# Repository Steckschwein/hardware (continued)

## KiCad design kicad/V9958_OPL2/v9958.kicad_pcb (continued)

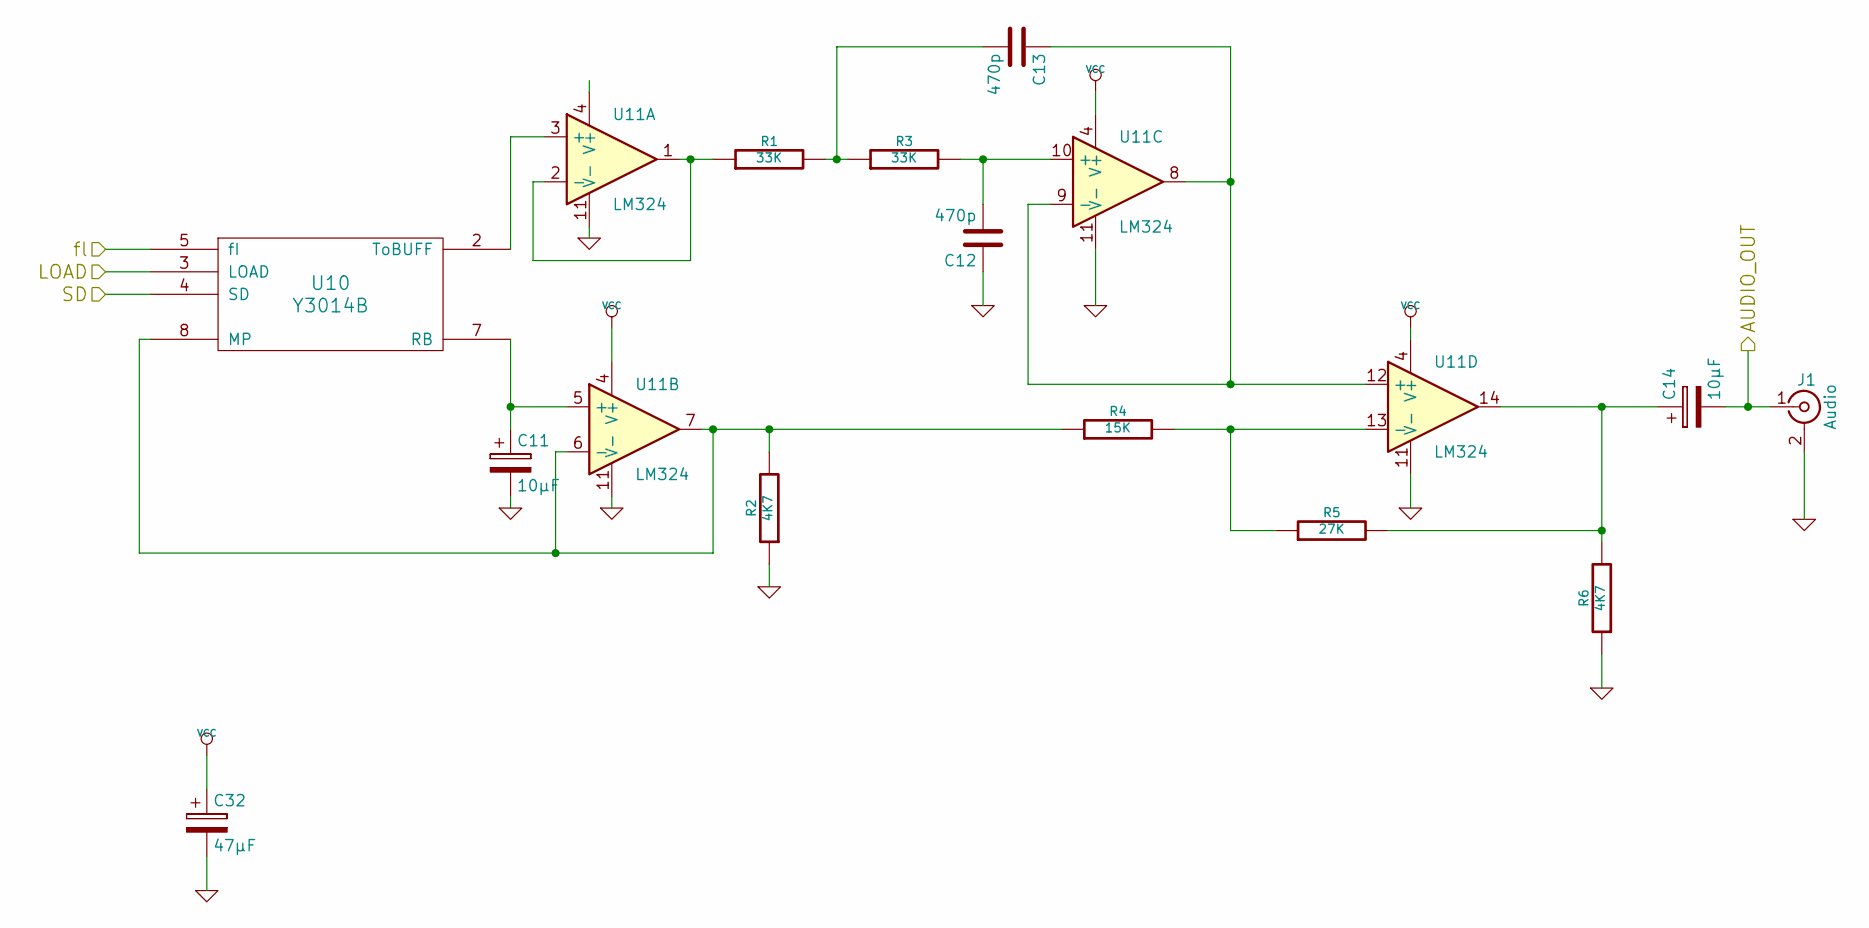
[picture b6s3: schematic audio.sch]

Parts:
C11, C14: 10µF; CP_Radial_D6.3mm_P2.50mm
C12, C13: 470p; C_Disc_D3.0mm_W1.6mm_P2.50mm
C32: 47µF; CP_Radial_D6.3mm_P2.50mm
J1: Audio; rca
R1, R3: 33K; R3
R2, R6: 4K7; R3
R4: 15K; R3
R5: 27K; R3
U10: Y3014B; DIP-8_W7.62mm_LongPads
U11: LM324; DIP-14_W7.62mm_LongPads

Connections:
/Audio/AUDIO_OUT: C14.2, J1.1 (In); also elsewhere on the board
/Audio/LOAD: U10.3 (LOAD); also elsewhere on the board
/Audio/SD: U10.4 (SD); also elsewhere on the board
/Audio/fl: U10.5 (fI); also elsewhere on the board
GND: C11.2, C12.1, C32.2, J1.2 (Ext), R2.1, R6.1, U10.6 (GND), U11.11 (V-); also elsewhere on the board
unnamed: C11.1, U10.7 (RB), U11.5 (+)
unnamed: C12.2, R3.2, U11.10 (+)
unnamed: C13.1, U11.8, U11.9 (-), U11.12 (+)
unnamed: C13.2, R1.2, R3.1
unnamed: C14.1, R5.2, R6.2, U11.14
unnamed: R1.1, U11.1, U11.2 (-)
unnamed: R2.2, R4.1, U10.8 (MP), U11.6 (-), U11.7
unnamed: R4.2, R5.1, U11.13 (-)
unnamed: U10.2 (ToBUFF), U11.3 (+)
VCC: C32.1, U10.1 (VCC), U11.4 (V+); also elsewhere on the board

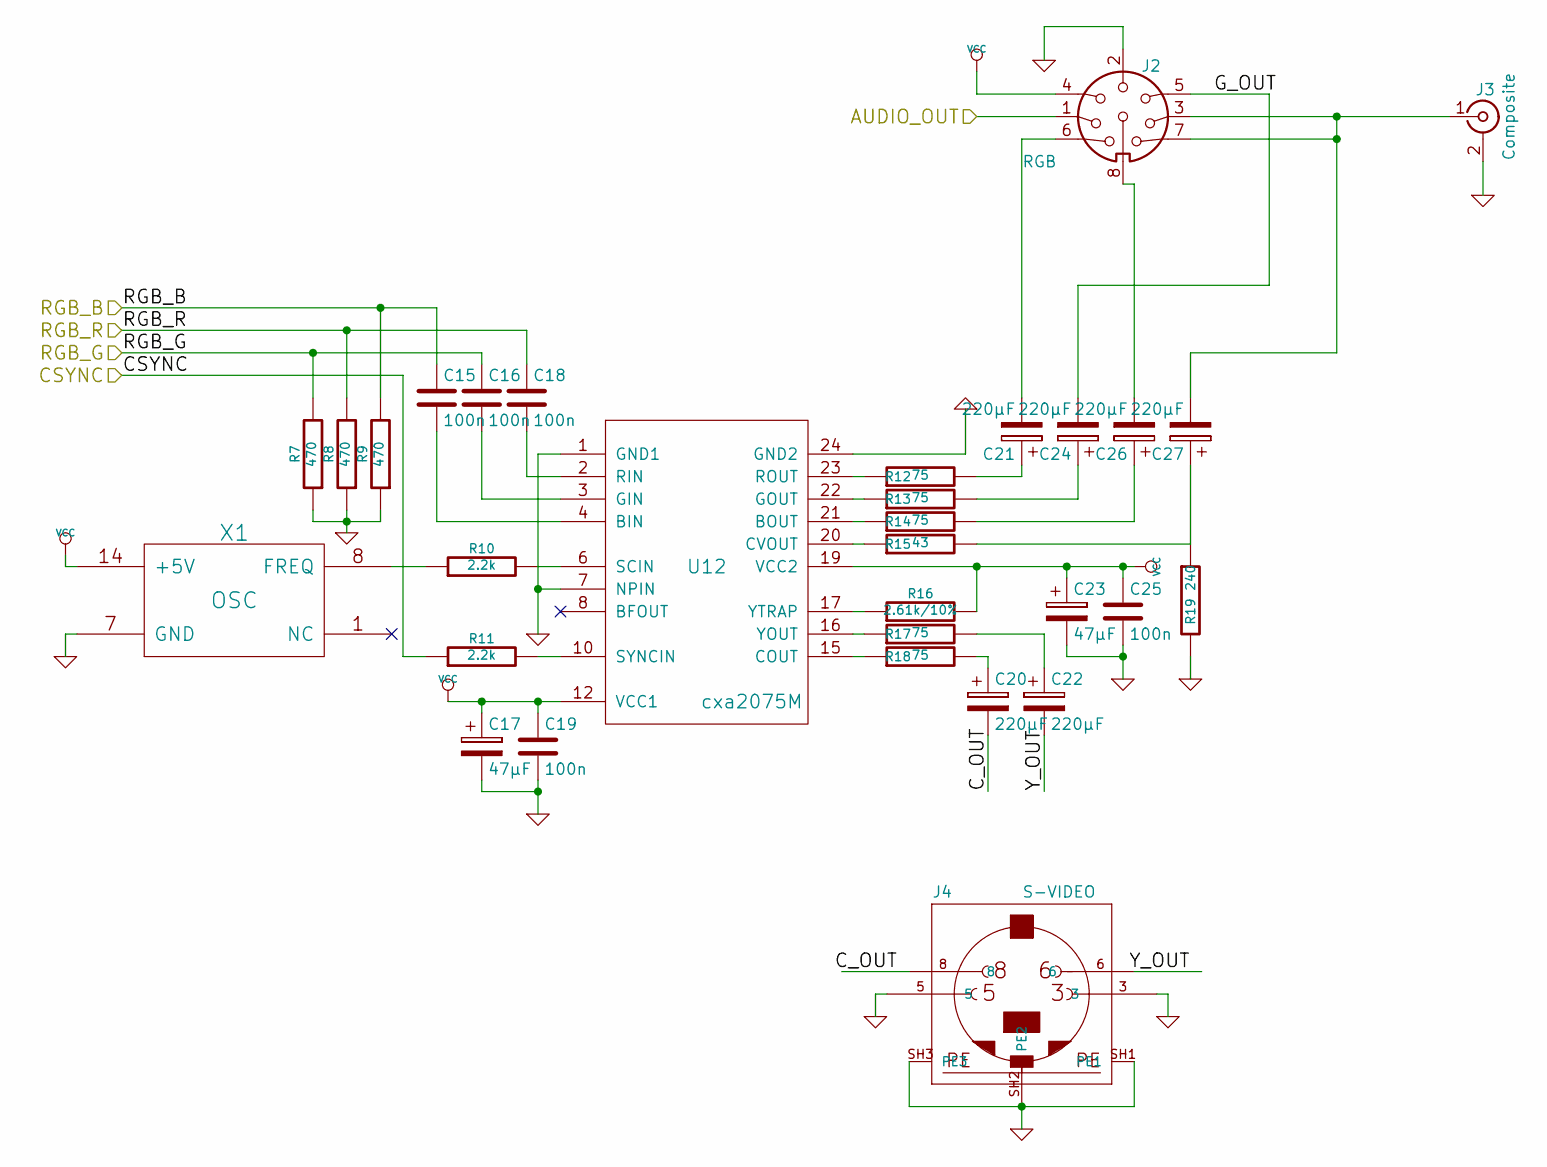
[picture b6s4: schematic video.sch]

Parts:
C15, C16, C18, C19: 100n; C_Disc_D3.0mm_W1.6mm_P2.50mm
C17, C23: 47µF; CP_Radial_D6.3mm_P2.50mm
C20, C21, C22, C24, C26, C27: 220µF; CP_Radial_D6.3mm_P2.50mm
C25: 100n; C_Disc_D3.0mm_W2.0mm_P2.50mm
J2: RGB; DIN-8
J3: Composite; rca
J4: S-VIDEO; mini_din-M_DIN4
R7, R8, R9: 470; R3
R10, R11: 2.2k; R3
R12, R13, R14, R17, R18: 75; R3
R15: 43; R3
R16: 2.61k/10%; R3
R19: 240; R3
U12: cxa2075M; SOIC-24W_7.5x15.4mm_Pitch1.27mm
X1: OSC; Oscillator_DIP-14_LargePads

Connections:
/Audio/AUDIO_OUT: J2.1; also elsewhere on the board
/CSYNC: R11.1; also elsewhere on the board
/RGB_B: C15.1, R9.2; also elsewhere on the board
/RGB_G: C16.1, R7.2; also elsewhere on the board
/RGB_R: C18.1, R8.2; also elsewhere on the board
/Video/C_OUT: C20.2, J4.8
/Video/G_OUT: C24.2, J2.5
/Video/Y_OUT: C22.2, J4.6
GND: C17.2, C19.2, C23.2, C25.2, J2.2, J3.2 (Ext), J4.3, J4.5, J4.SH1 (PE1), J4.SH2 (PE2), J4.SH3 (PE3), R7.1, R8.1, R9.1, R19.2, U12.1 (GND1), U12.7 (NPIN), U12.24 (GND2), X1.7 (GND); also elsewhere on the board
unnamed: C15.2, U12.4 (BIN)
unnamed: C16.2, U12.3 (GIN)
unnamed: C18.2, U12.2 (RIN)
unnamed: C20.1, R18.2
unnamed: C21.1, R12.2
unnamed: C21.2, J2.6
unnamed: C22.1, R17.2
unnamed: C24.1, R13.2
unnamed: C26.1, R14.2
unnamed: C26.2, J2.8
unnamed: C27.1, R15.2, R19.1
unnamed: C27.2, J2.3, J2.7, J3.1 (In)
unnamed: R10.1, X1.8 (FREQ)
unnamed: R10.2, U12.6 (SCIN)
unnamed: R11.2, U12.10 (SYNCIN)
unnamed: R12.1, U12.23 (ROUT)
unnamed: R13.1, U12.22 (GOUT)
unnamed: R14.1, U12.21 (BOUT)
unnamed: R15.1, U12.20 (CVOUT)
unnamed: R16.1, U12.17 (YTRAP)
unnamed: R17.1, U12.16 (YOUT)
unnamed: R18.1, U12.15 (COUT)
VCC: C17.1, C19.1, C23.1, C25.1, J2.4, R16.2, U12.12 (VCC1), U12.19 (VCC2), X1.14 (+5V); also elsewhere on the board

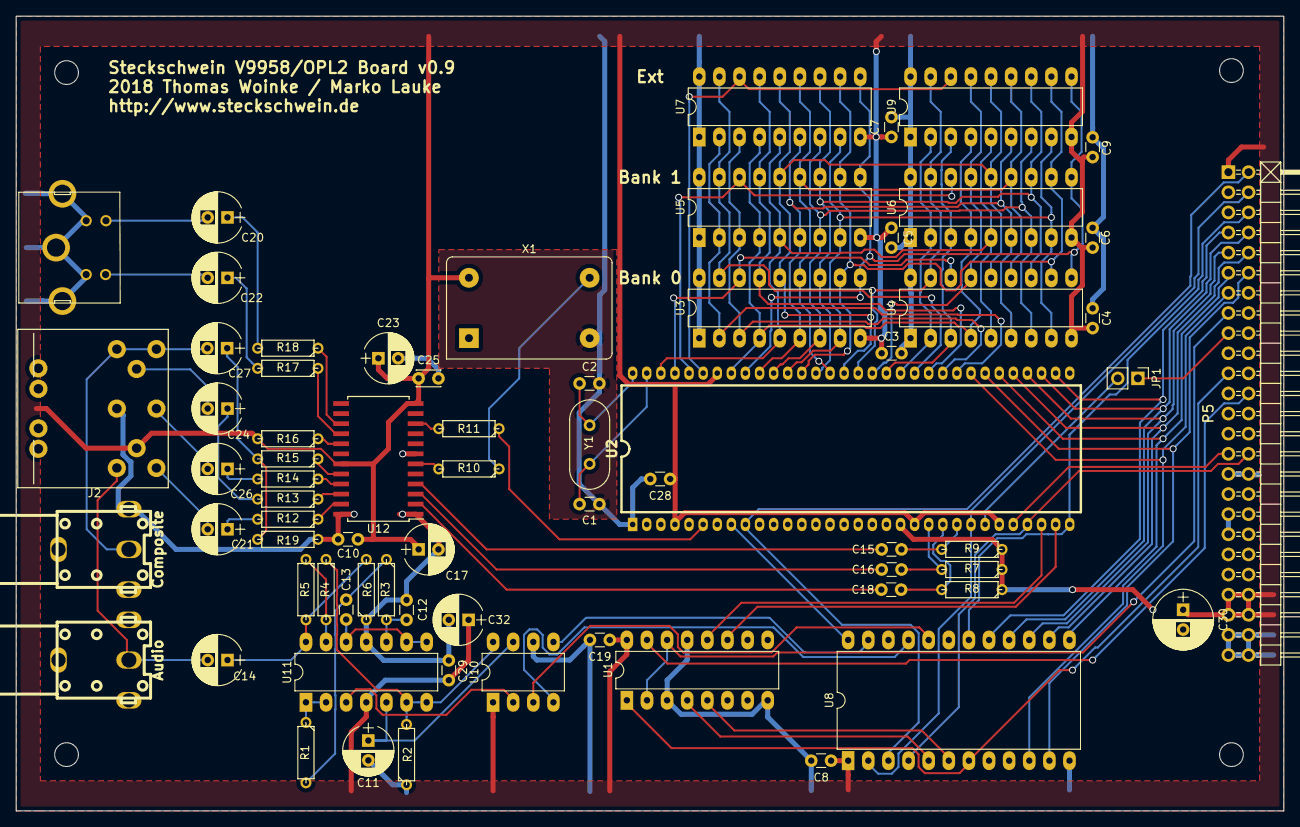
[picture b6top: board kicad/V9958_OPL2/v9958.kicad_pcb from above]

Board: 2 copper layers, 160.0 x 100.3 mm, 74 parts (0 on the bottom side), 89 nets.

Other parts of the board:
MH1, MH2, MH3, MH4: MountingHole_3mm_RevA_Date21Jun2010; MountingHole_3mm

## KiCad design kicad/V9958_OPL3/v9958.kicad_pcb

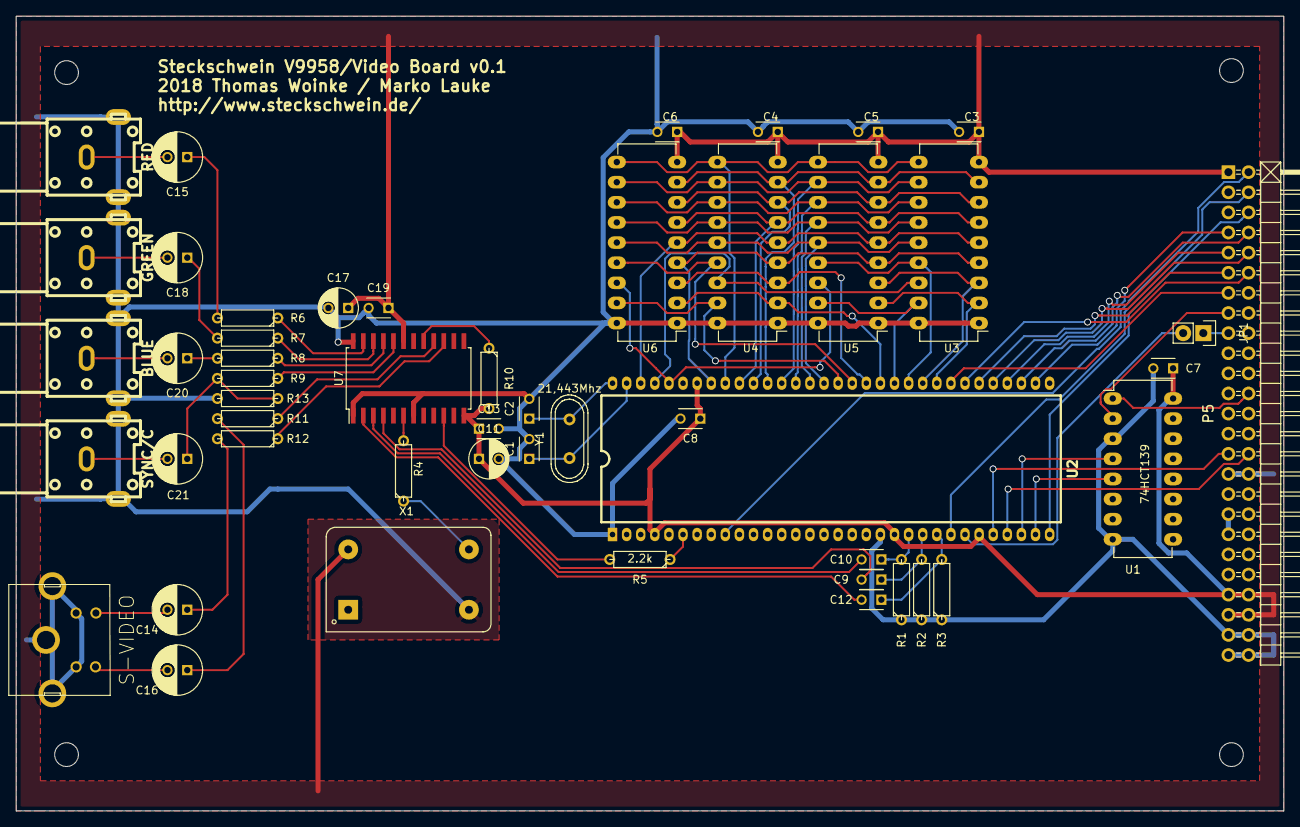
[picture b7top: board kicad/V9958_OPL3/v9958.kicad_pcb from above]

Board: 2 copper layers, 160.0 x 100.3 mm, 54 parts (0 on the bottom side), 71 nets.

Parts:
C1, C2: 22p; C_Disc_D3_P2.5
C3, C4, C5, C6, C7, C8, C9, C10, C12, C13, C19: 100n; C_Disc_D3_P2.5
C11, C17: 47µF; C_Radial_D5_L11_P2.5
C14, C15, C16, C18, C20, C21: 220µF; C_Radial_D6.3_L11.2_P2.5
JP1: JUMPER; Pin_Header_Straight_1x02
MH1, MH2, MH3, MH4: MountingHole_3mm_RevA_Date21Jun2010; MountingHole_3mm
P1: RED; rca_black
P2: GREEN; rca_black
P3: BLUE; rca_black
P4: SYNC/C; rca_black
P5: CONN_02X25; Pin_Header_Angled_2x25
R1, R2, R3: 470; R3
R4, R5: 2.2k; R3
R6, R7, R8, R11, R12: 75; R3
R9: 43; R3
R10: 2.61k/10%; R3
R13: 240; R3
U1: 74HCT139; DIP-16_W7.62mm_LongPads
U2: V9958; SDIP64
U3, U4, U5, U6: DRAM_64KX4; DIP-18_W7.62mm_LongPads
U7: cxa2075M; SOIC-24_7.5x15.4mm_Pitch1.27mm
X1: OSC; KXO-200_LargePads
X2: S-VIDEO; mini_din-M_DIN4
Y1: 21,443Mhz; Crystal_HC49-U_Vertical

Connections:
/50pin connector/A0: P5.30, U2.29
/50pin connector/A1: P5.29, U2.28
/50pin connector/D0: P5.13, U2.40
/50pin connector/D1: P5.12, U2.39
/50pin connector/D2: P5.11, U2.38
/50pin connector/D3: P5.10, U2.37
/50pin connector/D4: P5.9, U2.36
/50pin connector/D5: P5.8, U2.35
/50pin connector/D6: P5.7, U2.34
/50pin connector/D7: P5.6, U2.32
//CAS0: U2.61, U3.16, U4.16
//CAS1: U2.60, U5.16, U6.16
//RAS: U2.62, U3.5, U4.5, U5.5, U6.5
/AD0: U2.49, U3.14, U4.14, U5.14, U6.14
/AD1: U2.50, U3.13, U4.13, U5.13, U6.13
/AD2: U2.51, U3.12, U4.12, U5.12, U6.12
/AD3: U2.52, U3.11, U4.11, U5.11, U6.11
/AD4: U2.53, U3.8, U4.8, U5.8, U6.8
/AD5: U2.54, U3.7, U4.7, U5.7, U6.7
/AD6: U2.55, U3.6, U4.6, U5.6, U6.6
/AD7: U2.56, U3.10, U4.10, U5.10, U6.10
/CSYNC: R5.1, U2.6
/CS_VDP: P5.24, U1.1
/C_OUT: C14.2, X2.8
/IRQ: P5.4, U2.25
/R/W: U2.57, U3.4, U4.4, U5.4, U6.4
/RD0: U2.41, U3.2, U5.2
/RD1: U2.42, U3.3, U5.3
/RD2: U2.43, U3.15, U5.15
/RD3: U2.44, U3.17, U5.17
/RD4: U2.45, U4.2, U6.2
/RD5: U2.46, U4.3, U6.3
/RD6: U2.47, U4.15, U6.15
/RD7: U2.48, U4.17, U6.17
/RESET: P5.2, U2.9
/RGB_B: C12.1, R3.2, U2.24
/RGB_G: C10.1, R1.2, U2.22
/RGB_R: C9.1, R2.2, U2.23
/RW: P5.15, U1.2
/Y_OUT: C16.2, X2.6
GND: C1.2, C2.2, C3.2, C4.2, C5.2, C6.2, C7.2, C8.2, C11.2, C13.2, C17.2, C19.2, P1.2, P2.2, P3.2, P4.2, P5.31, P5.32, P5.35, P5.37, P5.47, P5.48, P5.49, P5.50, R1.1, R2.1, R3.1, R13.2, U1.3, U1.8, U2.1, U2.20, U3.1, U3.18, U4.1, U4.18, U5.1, U5.18, U6.1, U6.18, U7.1, U7.7, U7.24, X1.7, X2.3, X2.5, X2.SH1, X2.SH2, X2.SH3
unnamed: C1.1, U2.63, Y1.1
unnamed: C2.1, U2.64, Y1.2
unnamed: C9.2, U7.4
unnamed: C10.2, U7.3
unnamed: C12.2, U7.2
unnamed: C14.1, R12.2
unnamed: C15.1, R6.2
unnamed: C15.2, P1.1
unnamed: C16.1, R11.2
unnamed: C18.1, R7.2
unnamed: C18.2, P2.1
unnamed: C20.1, R8.2
unnamed: C20.2, P3.1
unnamed: C21.1, R9.2, R13.1
unnamed: C21.2, P4.1
unnamed: JP1.2, U2.26
unnamed: R4.1, X1.8
unnamed: R4.2, U7.6
unnamed: R5.2, U7.10
unnamed: R6.1, U7.23
unnamed: R7.1, U7.22
unnamed: R8.1, U7.21
unnamed: R9.1, U7.20
unnamed: R10.1, U7.17
unnamed: R11.1, U7.16
unnamed: R12.1, U7.15
unnamed: U1.4, U2.30
unnamed: U1.5, U2.31
RDY: JP1.1, P5.17
VCC: C3.1, C4.1, C5.1, C6.1, C7.1, C8.1, C11.1, C13.1, C17.1, C19.1, P5.1, P5.43, P5.44, P5.45, P5.46, R10.2, U1.16, U2.4, U2.21, U2.27, U2.58, U3.9, U4.9, U5.9, U6.9, U7.12, U7.19, X1.14

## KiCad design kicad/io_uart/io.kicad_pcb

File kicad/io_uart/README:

This is the IO-board with integrated UART.
This is the currently used board.

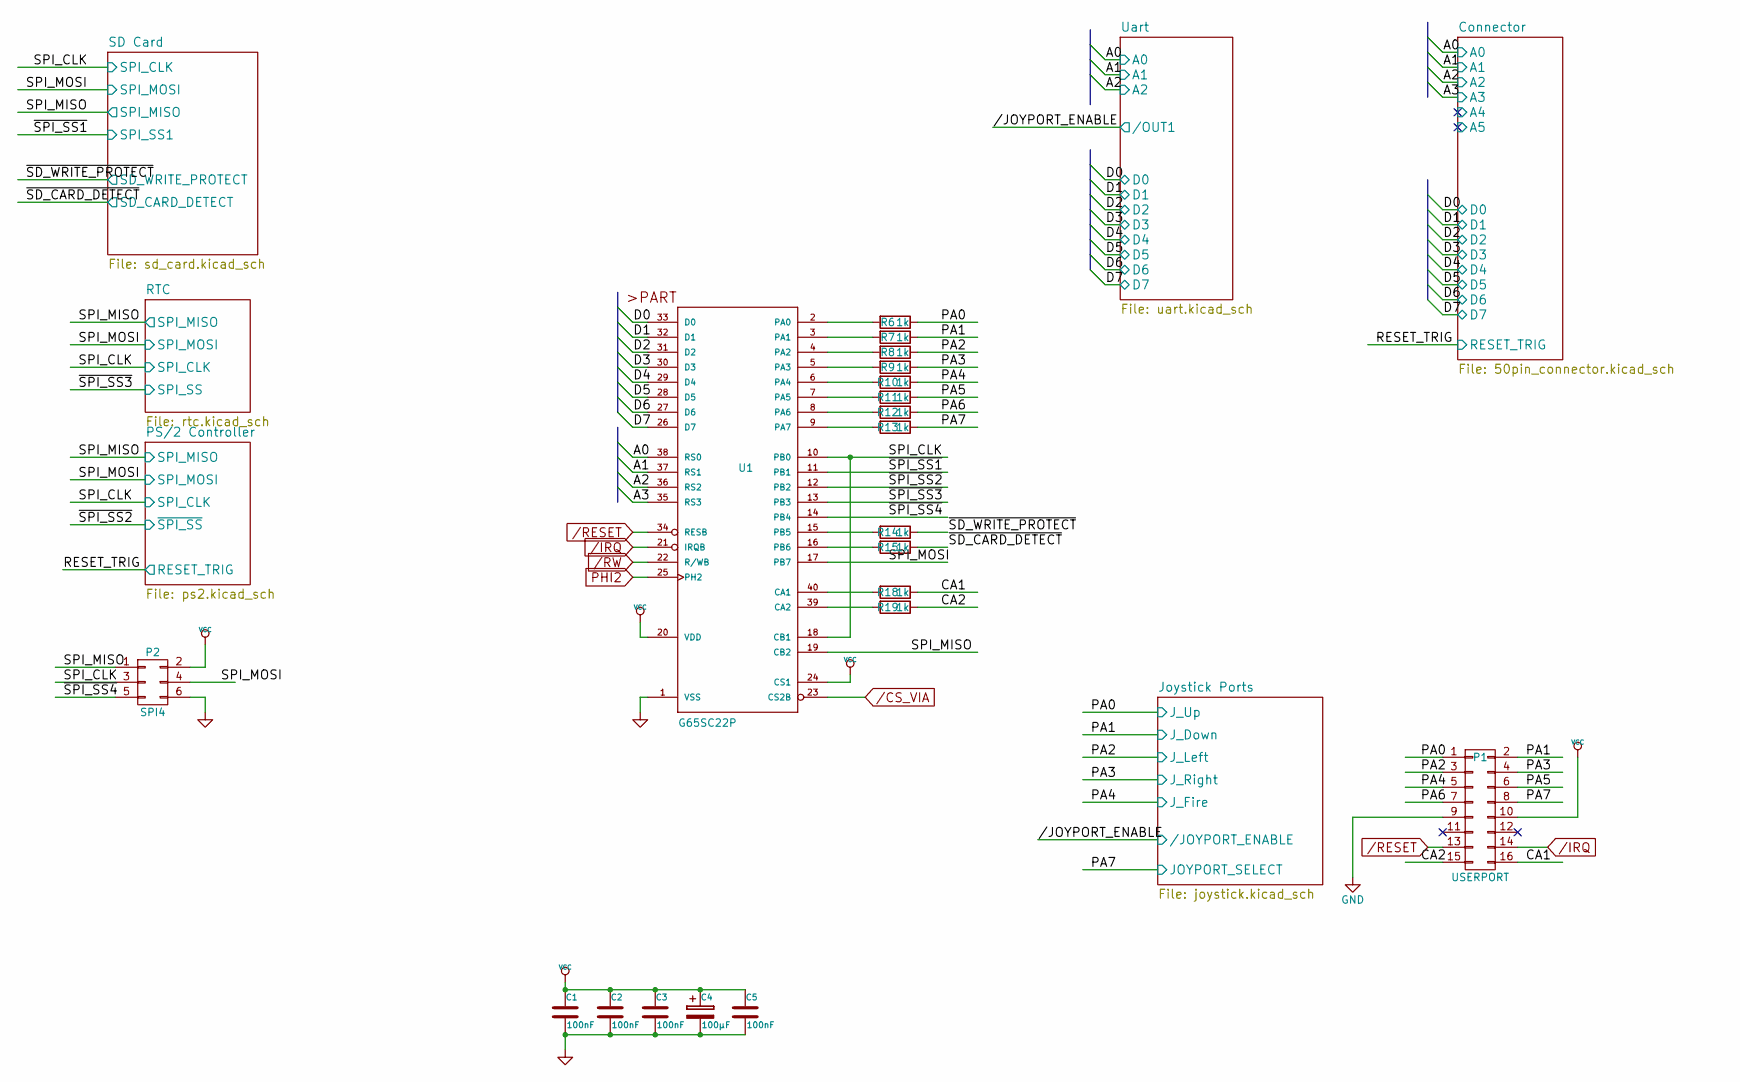
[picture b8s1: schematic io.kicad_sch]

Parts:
C1, C2, C3, C5: 100nF; C_Disc_D3_P2.5
C4: 100µF; C_Disc_D3_P2.5
P1: USERPORT; Pin_Header_Angled_2x08
P2: SPI4; Pin_Header_Angled_2x03
R6, R7, R8, R9, R10, R11, R12, R13, R14, R15, R18, R19: 1k; Resistor_Horizontal_RM7mm
U1: G65SC22P; DIP-40_W15.24mm_LongPads

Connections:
/CA1: P1.16, R18.1
/CA2: P1.15, R19.1
/CS_VIA: U1.23 (CS2B); also elsewhere on the board
/Connector/A0: U1.38 (RS0); also elsewhere on the board
/Connector/A1: U1.37 (RS1); also elsewhere on the board
/Connector/A2: U1.36 (RS2); also elsewhere on the board
/Connector/A3: U1.35 (RS3); also elsewhere on the board
/Connector/D0: U1.33 (D0); also elsewhere on the board
/Connector/D1: U1.32 (D1); also elsewhere on the board
/Connector/D2: U1.31 (D2); also elsewhere on the board
/Connector/D3: U1.30 (D3); also elsewhere on the board
/Connector/D4: U1.29 (D4); also elsewhere on the board
/Connector/D5: U1.28 (D5); also elsewhere on the board
/Connector/D6: U1.27 (D6); also elsewhere on the board
/Connector/D7: U1.26 (D7); also elsewhere on the board
/IRQ: P1.14, U1.21 (IRQB); also elsewhere on the board
/Joystick Ports/JOYPORT_SELECT: P1.8, R13.1; also elsewhere on the board
/Joystick Ports/J_Down: P1.2, R7.1; also elsewhere on the board
/Joystick Ports/J_Fire: P1.5, R10.1; also elsewhere on the board
/Joystick Ports/J_Left: P1.3, R8.1; also elsewhere on the board
/Joystick Ports/J_Right: P1.4, R9.1; also elsewhere on the board
/Joystick Ports/J_Up: P1.1, R6.1; also elsewhere on the board
/PA5: P1.6, R11.1
/PA6: P1.7, R12.1
/PS/2 Controller/SPI_CLK: P2.3, U1.10 (PB0), U1.18 (CB1); also elsewhere on the board
/PS/2 Controller/SPI_MISO: P2.1, U1.19 (CB2); also elsewhere on the board
/PS/2 Controller/SPI_MOSI: P2.4, U1.17 (PB7); also elsewhere on the board
/PS/2 Controller/~SPI_SS: U1.12 (PB2); also elsewhere on the board
/RESET: P1.13, U1.34 (RESB); also elsewhere on the board
/RTC/SPI_SS: U1.13 (PB3); also elsewhere on the board
/RW: U1.22 (R/WB); also elsewhere on the board
/SD Card/SD_CARD_DETECT: R15.1; also elsewhere on the board
/SD Card/SD_WRITE_PROTECT: R14.1; also elsewhere on the board
/SD Card/SPI_SS1: U1.11 (PB1); also elsewhere on the board
/~SPI_SS4: P2.5, U1.14 (PB4)
GND: C1.2, C2.2, C3.2, C4.2, C5.2, P1.9, P2.6, U1.1 (VSS); also elsewhere on the board
unnamed: R6.2, U1.2 (PA0)
unnamed: R7.2, U1.3 (PA1)
unnamed: R8.2, U1.4 (PA2)
unnamed: R9.2, U1.5 (PA3)
unnamed: R10.2, U1.6 (PA4)
unnamed: R11.2, U1.7 (PA5)
unnamed: R12.2, U1.8 (PA6)
unnamed: R13.2, U1.9 (PA7)
unnamed: R14.2, U1.15 (PB5)
unnamed: R15.2, U1.16 (PB6)
unnamed: R18.2, U1.40 (CA1)
unnamed: R19.2, U1.39 (CA2)
PHI2: U1.25 (PH2); also elsewhere on the board
VCC: C1.1, C2.1, C3.1, C4.1, C5.1, P1.10, P2.2, U1.20 (VDD), U1.24 (CS1); also elsewhere on the board

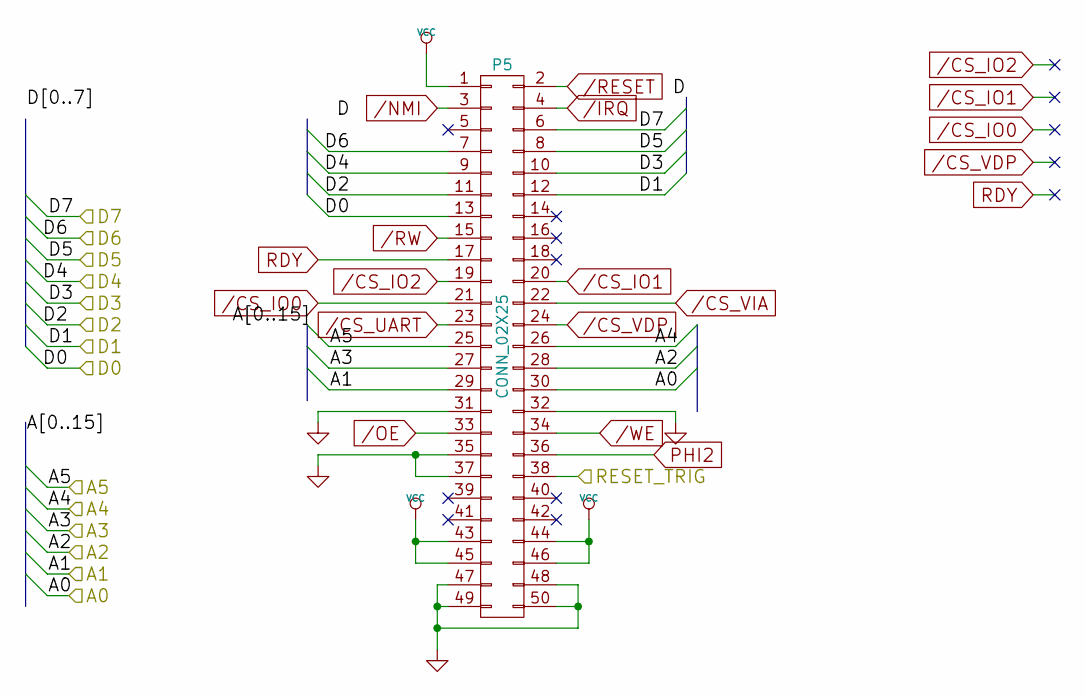
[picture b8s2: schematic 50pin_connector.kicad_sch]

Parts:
P5: CONN_02X25; Pin_Header_Angled_2x25

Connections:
/CS_IO0: P5.21
/CS_IO1: P5.20
/CS_IO2: P5.19
/CS_UART: P5.23; also elsewhere on the board
/CS_VDP: P5.24
/CS_VIA: P5.22; also elsewhere on the board
/Connector/A0: P5.30; also elsewhere on the board
/Connector/A1: P5.29; also elsewhere on the board
/Connector/A2: P5.28; also elsewhere on the board
/Connector/A3: P5.27; also elsewhere on the board
/Connector/A4: P5.26
/Connector/A5: P5.25
/Connector/D0: P5.13; also elsewhere on the board
/Connector/D1: P5.12; also elsewhere on the board
/Connector/D2: P5.11; also elsewhere on the board
/Connector/D3: P5.10; also elsewhere on the board
/Connector/D4: P5.9; also elsewhere on the board
/Connector/D5: P5.8; also elsewhere on the board
/Connector/D6: P5.7; also elsewhere on the board
/Connector/D7: P5.6; also elsewhere on the board
/Connector/RESET_TRIG: P5.38; also elsewhere on the board
/IRQ: P5.4; also elsewhere on the board
/NMI: P5.3; also elsewhere on the board
/OE: P5.33; also elsewhere on the board
/RESET: P5.2; also elsewhere on the board
/RW: P5.15; also elsewhere on the board
/WE: P5.34; also elsewhere on the board
GND: P5.31, P5.32, P5.35, P5.37, P5.47, P5.48, P5.49, P5.50; also elsewhere on the board
PHI2: P5.36; also elsewhere on the board
RDY: P5.17
VCC: P5.1, P5.43, P5.44, P5.45, P5.46; also elsewhere on the board

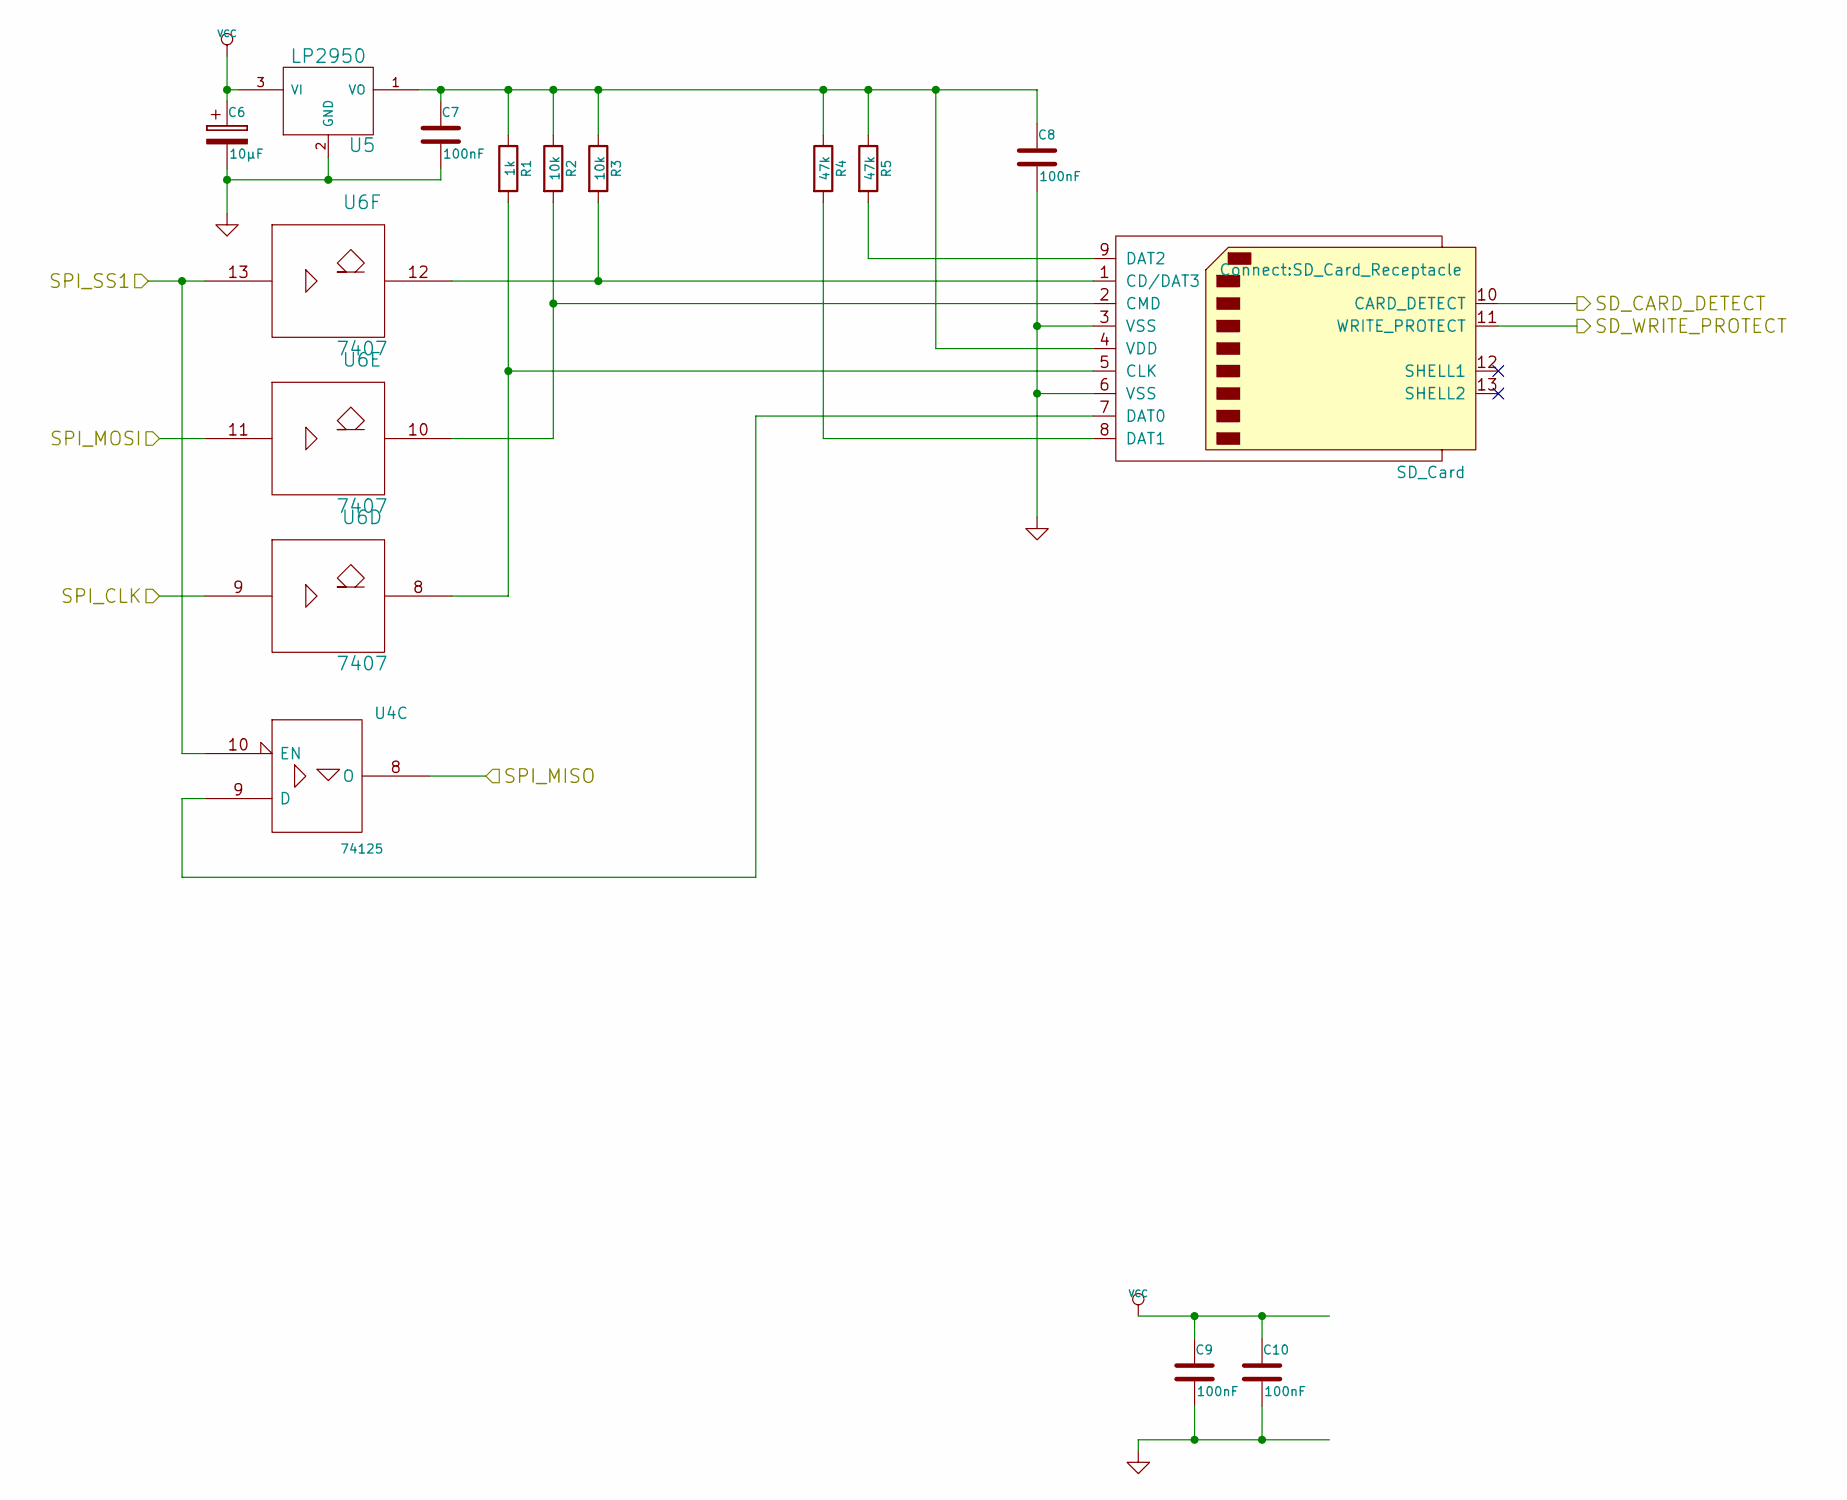
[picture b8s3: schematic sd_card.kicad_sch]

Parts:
C6: 10µF; C_Radial_D5_L6_P2.5
C7, C8, C9, C10: 100nF; C_Disc_D3_P2.5
R1: 1k; Resistor_Horizontal_RM7mm
R2, R3: 10k; Resistor_Horizontal_RM7mm
R4, R5: 47k; Resistor_Horizontal_RM7mm
U4: 74125; DIP-14_W7.62mm_LongPads
U5: LP2950; TO-92_Inline_Narrow_Oval
U6: 7407; DIP-14_W7.62mm_LongPads

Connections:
/PS/2 Controller/SPI_CLK: U6.9; also elsewhere on the board
/PS/2 Controller/SPI_MISO: U4.8 (O); also elsewhere on the board
/PS/2 Controller/SPI_MOSI: U6.11; also elsewhere on the board
/SD Card/SPI_SS1: U4.10 (EN), U6.13; also elsewhere on the board
GND: C6.2, C7.2, C8.2, C9.2, C10.2, U4.7 (GND), U5.2 (GND), U6.7 (Gnd); also elsewhere on the board
unnamed 49: C7.1, C8.1, R1.1, R2.1, R3.1, R4.1, R5.1, U5.1 (VO); also elsewhere on the board
unnamed 103: R1.2, U6.8; also elsewhere on the board
unnamed 104: R2.2, U6.10; also elsewhere on the board
unnamed 105: R3.2, U6.12; also elsewhere on the board
unnamed 106: R4.2; also elsewhere on the board
unnamed 107: R5.2; also elsewhere on the board
unnamed 121: U4.9 (D); also elsewhere on the board
VCC: C6.1, C9.1, C10.1, U4.14 (VCC), U5.3 (VI), U6.14 (Vcc); also elsewhere on the board

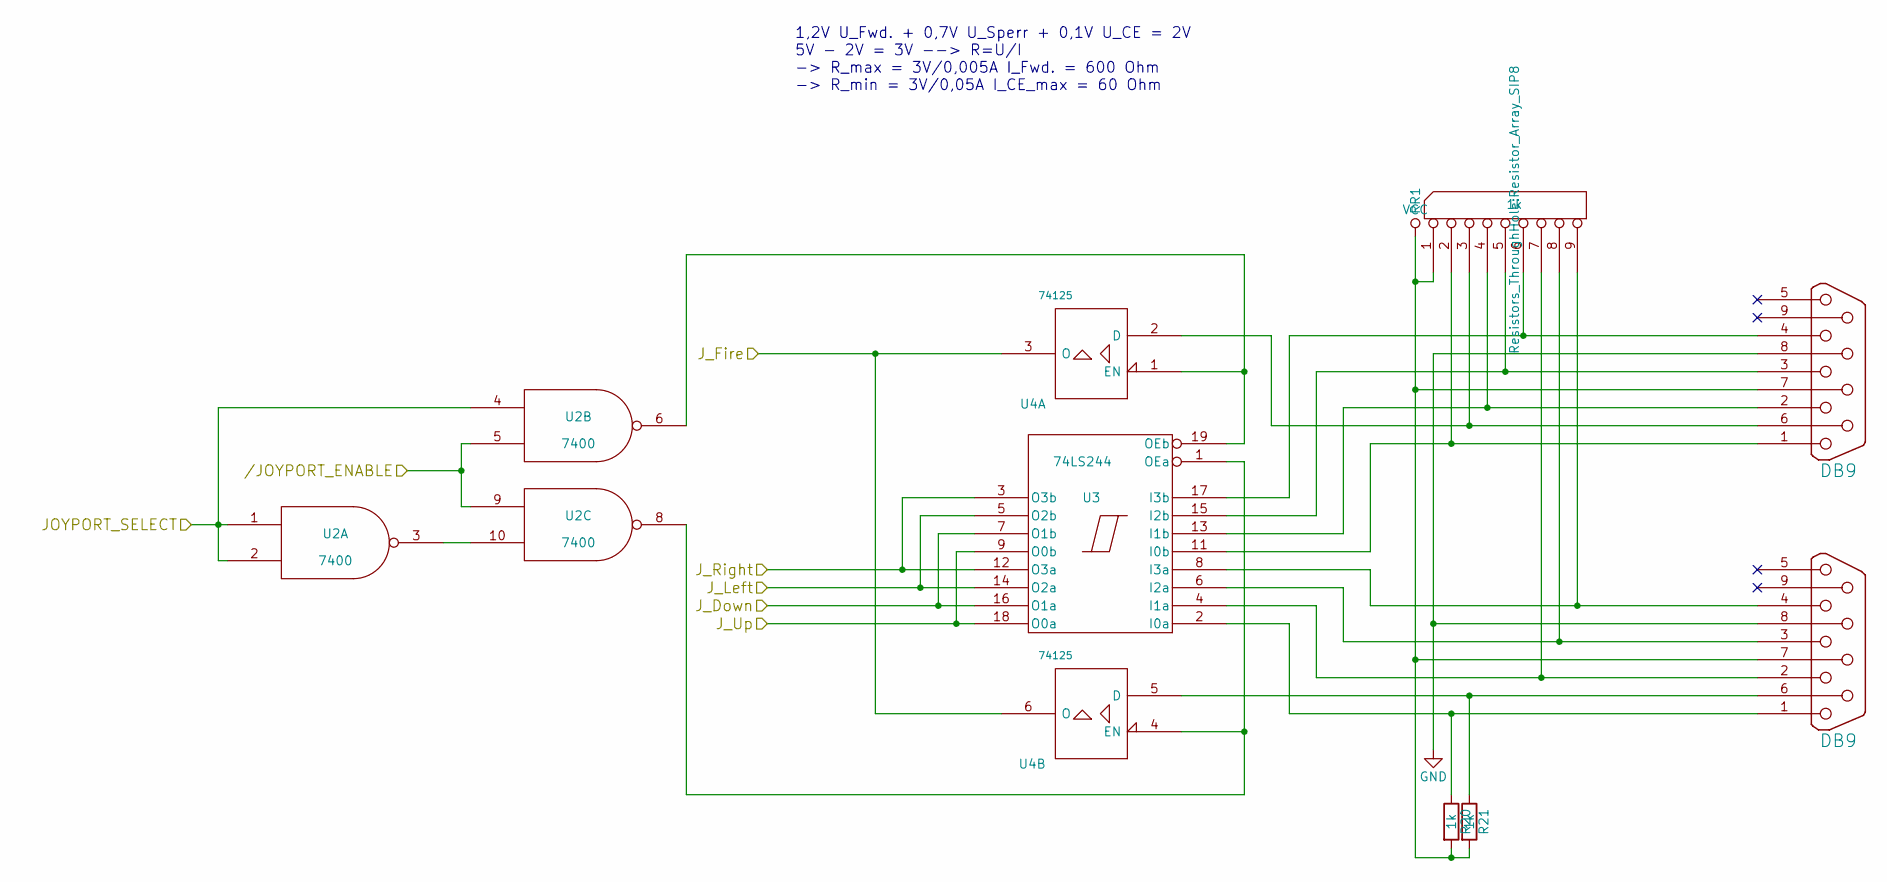
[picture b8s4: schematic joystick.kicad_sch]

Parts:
R20, R21: 1k; Resistor_Horizontal_RM7mm
RR1: 1k; Resistor_Array_SIP8
U2: 7400; DIP-14_W7.62mm_LongPads
U3: 74LS244; DIP-20_W7.62mm_LongPads
U4: 74125; DIP-14_W7.62mm_LongPads

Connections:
/Joystick Ports//JOYPORT_ENABLE: U2.5, U2.9; also elsewhere on the board
/Joystick Ports/JOYPORT_SELECT: U2.1, U2.2, U2.4; also elsewhere on the board
/Joystick Ports/J_Down: U3.7 (O1b), U3.16 (O1a); also elsewhere on the board
/Joystick Ports/J_Fire: U4.3 (O), U4.6 (O); also elsewhere on the board
/Joystick Ports/J_Left: U3.5 (O2b), U3.14 (O2a); also elsewhere on the board
/Joystick Ports/J_Right: U3.3 (O3b), U3.12 (O3a); also elsewhere on the board
/Joystick Ports/J_Up: U3.9 (O0b), U3.18 (O0a); also elsewhere on the board
GND: U2.7 (GND), U3.10 (GND), U4.7 (GND); also elsewhere on the board
unnamed 89: RR1.2, U3.11 (I0b); also elsewhere on the board
unnamed 90: RR1.4, U3.13 (I1b); also elsewhere on the board
unnamed 91: RR1.5, U3.15 (I2b); also elsewhere on the board
unnamed 92: RR1.6, U3.17 (I3b); also elsewhere on the board
unnamed 94: RR1.3, U4.2 (D); also elsewhere on the board
unnamed 96: R20.1, U3.2 (I0a); also elsewhere on the board
unnamed 97: RR1.7, U3.4 (I1a); also elsewhere on the board
unnamed 98: RR1.8, U3.6 (I2a); also elsewhere on the board
unnamed 99: RR1.9, U3.8 (I3a); also elsewhere on the board
unnamed 101: R21.1, U4.5 (D); also elsewhere on the board
unnamed: U2.6, U3.19 (OEb), U4.1 (EN)
unnamed: U2.8, U3.1 (OEa), U4.4 (EN)
unnamed: U2.3, U2.10
VCC: R20.2, R21.2, RR1.1 (COM), U2.14 (VCC), U3.20 (VCC), U4.14 (VCC); also elsewhere on the board

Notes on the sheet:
1,2V U_Fwd. + 0,7V U_Sperr + 0,1V U_CE = 2V 5V - 2V = 3V --> R=U/I -> R_max = 3V/0,005A I_Fwd. = 600 Ohm -> R_min = 3V/0,05A I_CE_max = 60 Ohm
